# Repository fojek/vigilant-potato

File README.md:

# vigilant-potato
Capteur WiFi générique pour la cabane

* WIFI : ESP-12F ou ESP-M3
* MCU : Atmel ou ESP ou STM
* DC/DC à partir d'une alimentation 24V
* Adresse modifiable, par exemple DIP switch rotative

* Possibilité de lire: 
- distance ; 
- température ; 
- pression ;
- 2 entrées digitales ;

* Possibilité d'écrire :
- deux sorties relais?

Capteur ultrason modulaire (et autres capteurs)

Affichage de l'état : 
 - Vert clignotant : ON et en train de se connecter
 - Vert solide : ON et connecté
 - Autre led : Rouge si erreur (ou la même avec une autre séquence)
 - Autre led : trig effectué (distance)

Todo
- [ ] Déterminer un format
- [ ] Choisir ESP et MCU
- [ ] Choisir capteur ultrason
- [ ] Fabriquer PCB et tester

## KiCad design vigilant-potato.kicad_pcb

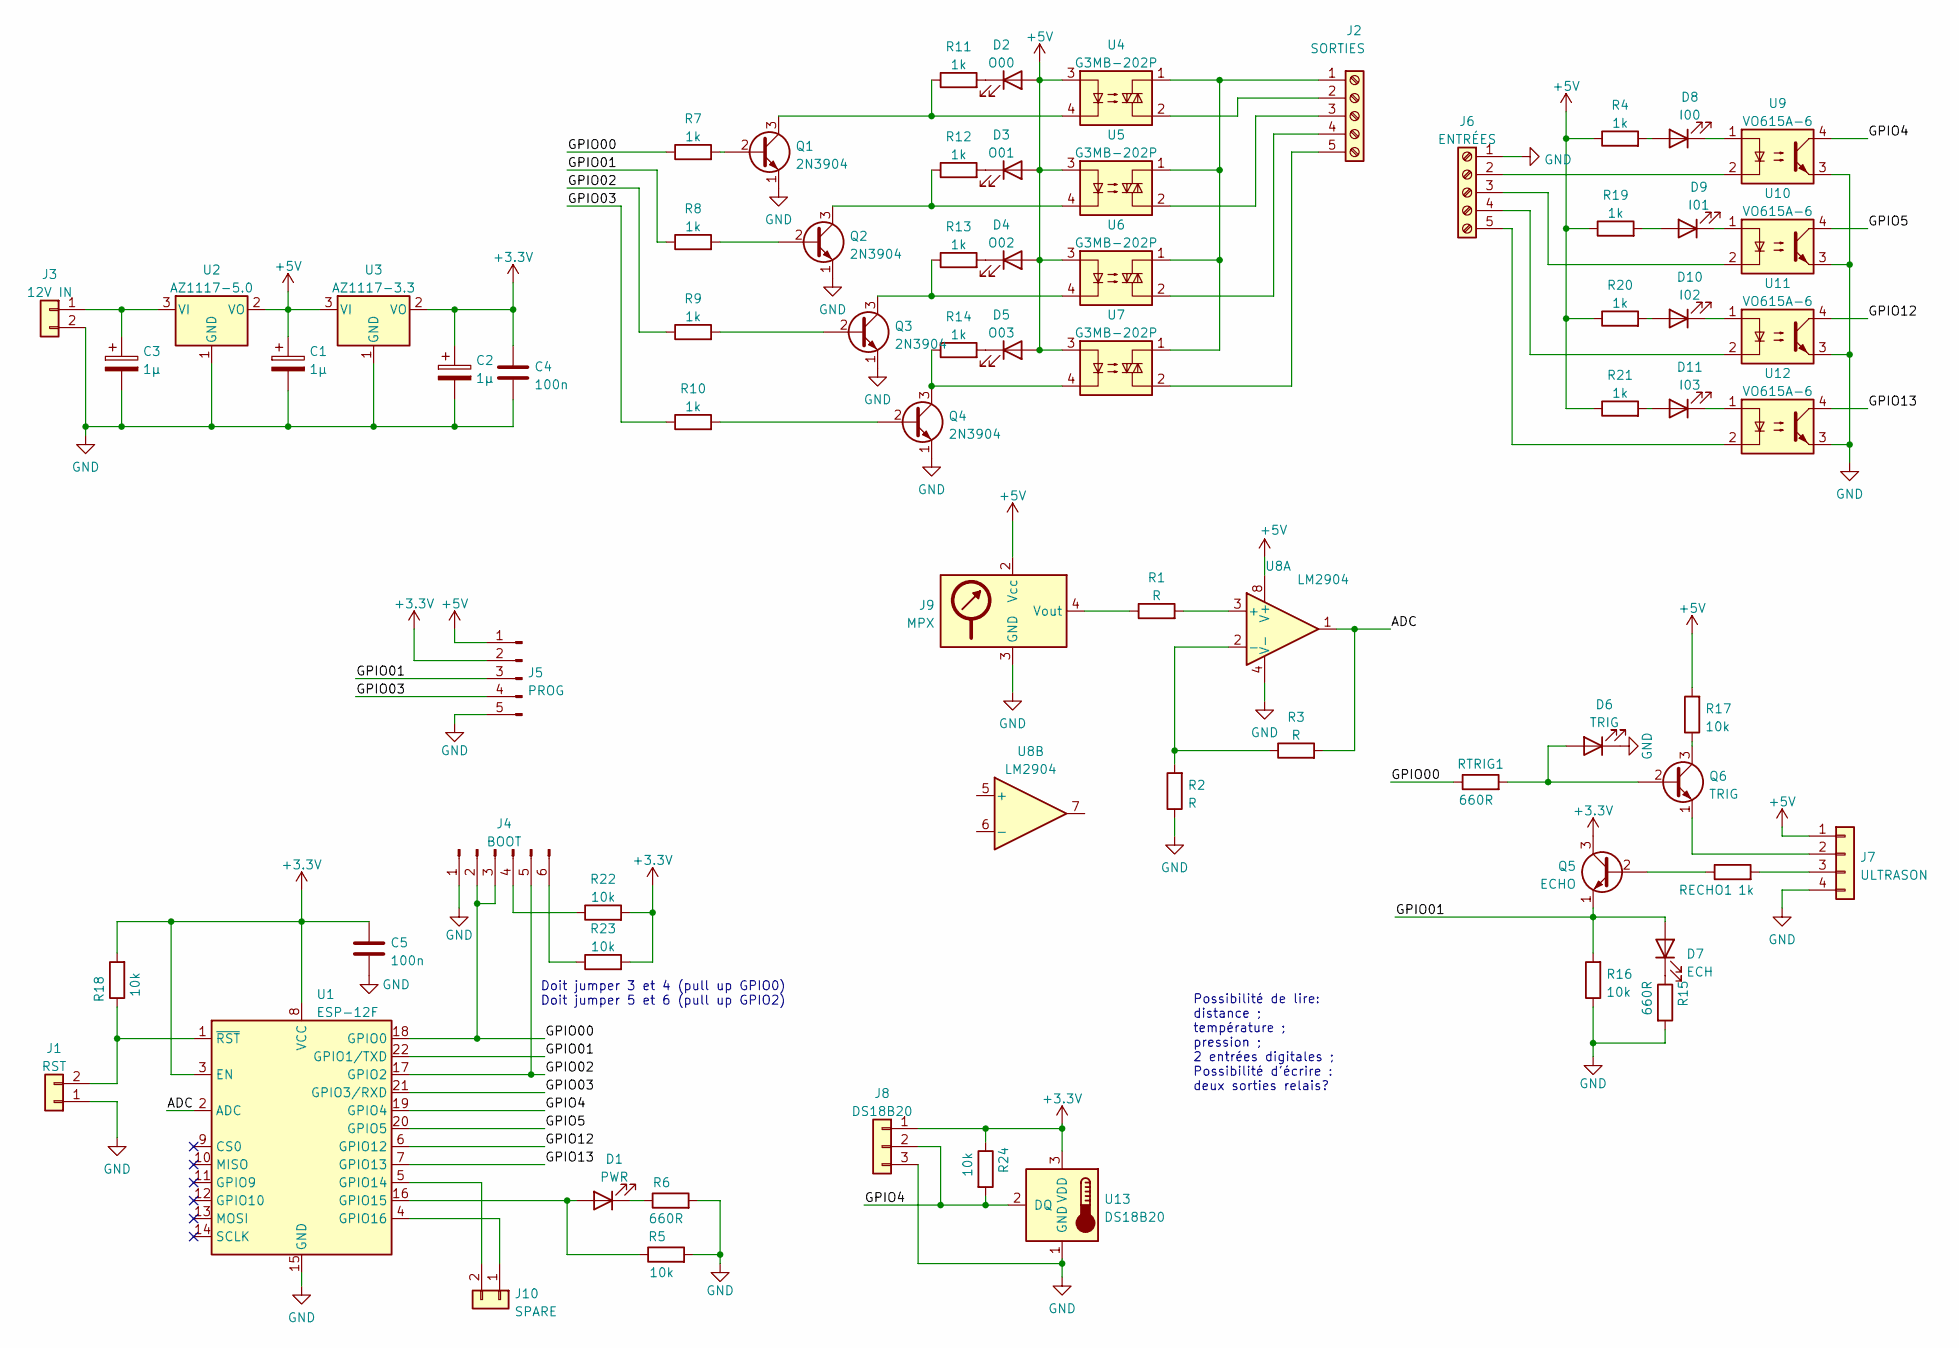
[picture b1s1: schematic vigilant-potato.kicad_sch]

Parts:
C1, C2, C3: 1µ; C_Rect_L7.0mm_W2.0mm_P5.00mm
C4, C5: 100n; C_Rect_L7.0mm_W2.0mm_P5.00mm
D1: PWR; LED_1206_3216Metric_Pad1.42x1.75mm_HandSolder
D2: O00; LED_1206_3216Metric_Pad1.42x1.75mm_HandSolder
D3: O01; LED_1206_3216Metric_Pad1.42x1.75mm_HandSolder
D4: O02; LED_1206_3216Metric_Pad1.42x1.75mm_HandSolder
D5: O03; LED_1206_3216Metric_Pad1.42x1.75mm_HandSolder
D6: TRIG; LED_1206_3216Metric_Pad1.42x1.75mm_HandSolder
D7: ECH; LED_1206_3216Metric_Pad1.42x1.75mm_HandSolder
D8: I00; LED_1206_3216Metric_Pad1.42x1.75mm_HandSolder
D9: I01; LED_1206_3216Metric_Pad1.42x1.75mm_HandSolder
D10: I02; LED_1206_3216Metric_Pad1.42x1.75mm_HandSolder
D11: I03; LED_1206_3216Metric_Pad1.42x1.75mm_HandSolder
J1: RST; PinHeader_1x02_P2.54mm_Vertical
J2: SORTIES; PhoenixContact_MCV_1,5_5-G-3.5_1x05_P3.50mm_Vertical; part EBRA-05-A
J3: 12V IN; PhoenixContact_MCV_1,5_2-G-3.5_1x02_P3.50mm_Vertical; part EBRA-02-A
J4: BOOT; PinHeader_1x06_P2.54mm_Vertical
J5: PROG; PinHeader_1x05_P2.54mm_Vertical
J6: ENTRÉES; PhoenixContact_MCV_1,5_5-G-3.5_1x05_P3.50mm_Vertical; part EBRA-05-A
J7: ULTRASON; PhoenixContact_MCV_1,5_4-G-3.5_1x04_P3.50mm_Vertical; part EBRA-04-A
J8: DS18B20; PinSocket_1x03_P2.54mm_Vertical
J9: MPX; PinHeader_1x06_P2.54mm_Vertical
J10: SPARE; PinHeader_1x02_P2.54mm_Vertical
Q1, Q2, Q3, Q4: 2N3904; TO-92_Inline
Q5: ECHO; TO-92_Inline
Q6: TRIG; TO-92_Inline
R1, R2, R3: R; R_Axial_DIN0207_L6.3mm_D2.5mm_P10.16mm_Horizontal
R4, R11, R12, R13, R14, R19, R20, R21: 1k; R_0805_2012Metric_Pad1.20x1.40mm_HandSolder
R5, R18, R22, R23: 10k; R_0805_2012Metric_Pad1.20x1.40mm_HandSolder
R6: 660R; R_0805_2012Metric_Pad1.20x1.40mm_HandSolder
R7, R8, R9, R10: 1k; R_Axial_DIN0207_L6.3mm_D2.5mm_P10.16mm_Horizontal
R15: 660R; R_Axial_DIN0207_L6.3mm_D2.5mm_P10.16mm_Horizontal
R16, R17, R24: 10k; R_Axial_DIN0207_L6.3mm_D2.5mm_P10.16mm_Horizontal
RECHO1: 1k; R_Axial_DIN0207_L6.3mm_D2.5mm_P10.16mm_Horizontal
RTRIG1: 660R; R_Axial_DIN0207_L6.3mm_D2.5mm_P10.16mm_Horizontal
U1: ESP-12F; ESP-12E
U2: AZ1117-5.0; TO-252-2
U3: AZ1117-3.3; TO-252-2
U4, U5, U6, U7: G3MB-202P
U8: LM2904; SOIC-8_3.9x4.9mm_P1.27mm
U9, U10, U11, U12: VO615A-6; DIP-4_W7.62mm
U13: DS18B20; TO-92_Inline

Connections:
+3.3V: C2.1, C4.1, C5.1, J5.2, J8.1, Q5.3 (C), R18.2, R22.2, R23.2, R24.1, U1.3 (EN), U1.8 (VCC), U3.2 (VO), U13.3 (VDD)
+5V: C1.1, D2.2 (A), D3.2 (A), D4.2 (A), D5.2 (A), J5.1, J7.1, J9.2 (Vcc), R4.1, R17.2, R19.1, R20.1, R21.1, U2.2 (VO), U3.3 (VI), U4.3, U5.3, U6.3, U7.3, U8.8 (V+)
/ADC: R3.2, U1.2 (ADC), U8.1
/GPIO00: J4.2, J4.3, R7.1, RTRIG1.1, U1.18 (GPIO0)
/GPIO01: D7.2 (A), J5.3, Q5.1 (E), R8.1, R16.2, U1.22 (GPIO1/TXD)
/GPIO02: J4.5, R9.1, U1.17 (GPIO2)
/GPIO03: J5.4, R10.1, U1.21 (GPIO3/RXD)
/GPIO4: J8.2, R24.2, U1.19 (GPIO4), U9.4, U13.2 (DQ)
/GPIO5: U1.20 (GPIO5), U10.4
/GPIO12: U1.6 (GPIO12), U11.4
/GPIO13: U1.7 (GPIO13), U12.4
GND: C1.2, C2.2, C3.2, C4.2, C5.2, D6.1 (K), J1.1, J3.2, J4.1, J5.5, J6.1, J7.4, J8.3, J9.3 (GND), Q1.1 (E), Q2.1 (E), Q3.1 (E), Q4.1 (E), R2.1, R5.2, R6.2, R15.2, R16.1, U1.15 (GND), U2.1 (GND), U3.1 (GND), U8.4 (V-), U9.3, U10.3, U11.3, U12.3, U13.1 (GND)
unnamed: C3.1, J3.1, U2.3 (VI)
unnamed: D1.1 (K), R6.1
unnamed: D1.2 (A), R5.1, U1.16 (GPIO15)
unnamed: D2.1 (K), R11.2
unnamed: D3.1 (K), R12.2
unnamed: D4.1 (K), R13.2
unnamed: D5.1 (K), R14.2
unnamed: D6.2 (A), Q6.2 (B), RTRIG1.2
unnamed: D7.1 (K), R15.1
unnamed: D8.1 (K), U9.1
unnamed: D8.2 (A), R4.2
unnamed: D9.1 (K), U10.1
unnamed: D9.2 (A), R19.2
unnamed: D10.1 (K), U11.1
unnamed: D10.2 (A), R20.2
unnamed: D11.1 (K), U12.1
unnamed: D11.2 (A), R21.2
unnamed: J1.2, R18.1, U1.1 (~RST)
unnamed: J2.1, U4.1, U5.1, U6.1, U7.1
unnamed: J2.2, U4.2
unnamed: J2.3, U5.2
unnamed: J2.4, U6.2
unnamed: J2.5, U7.2
unnamed: J4.4, R22.1
unnamed: J4.6, R23.1
unnamed: J6.2, U9.2
unnamed: J6.3, U10.2
unnamed: J6.4, U11.2
unnamed: J6.5, U12.2
unnamed: J7.2, Q6.1 (E)
unnamed: J7.3, RECHO1.2
unnamed: J9.4 (Vout), R1.1
unnamed: J10.1, U1.4 (GPIO16)
unnamed: J10.2, U1.5 (GPIO14)
unnamed: Q1.2 (B), R7.2
unnamed: Q1.3 (C), R11.1, U4.4
unnamed: Q2.2 (B), R8.2
unnamed: Q2.3 (C), R12.1, U5.4
unnamed: Q3.2 (B), R9.2
unnamed: Q3.3 (C), R13.1, U6.4
unnamed: Q4.2 (B), R10.2
unnamed: Q4.3 (C), R14.1, U7.4
unnamed: Q5.2 (B), RECHO1.1
unnamed: Q6.3 (C), R17.1
unnamed: R1.2, U8.3 (+)
unnamed: R2.2, R3.1, U8.2 (-)

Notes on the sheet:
Doit jumper 3 et 4 (pull up GPIO0) Doit jumper 5 et 6 (pull up GPIO2)
Possibilité de lire: distance ; température ; pression ; 2 entrées digitales ; Possibilité d'écrire : deux sorties relais?

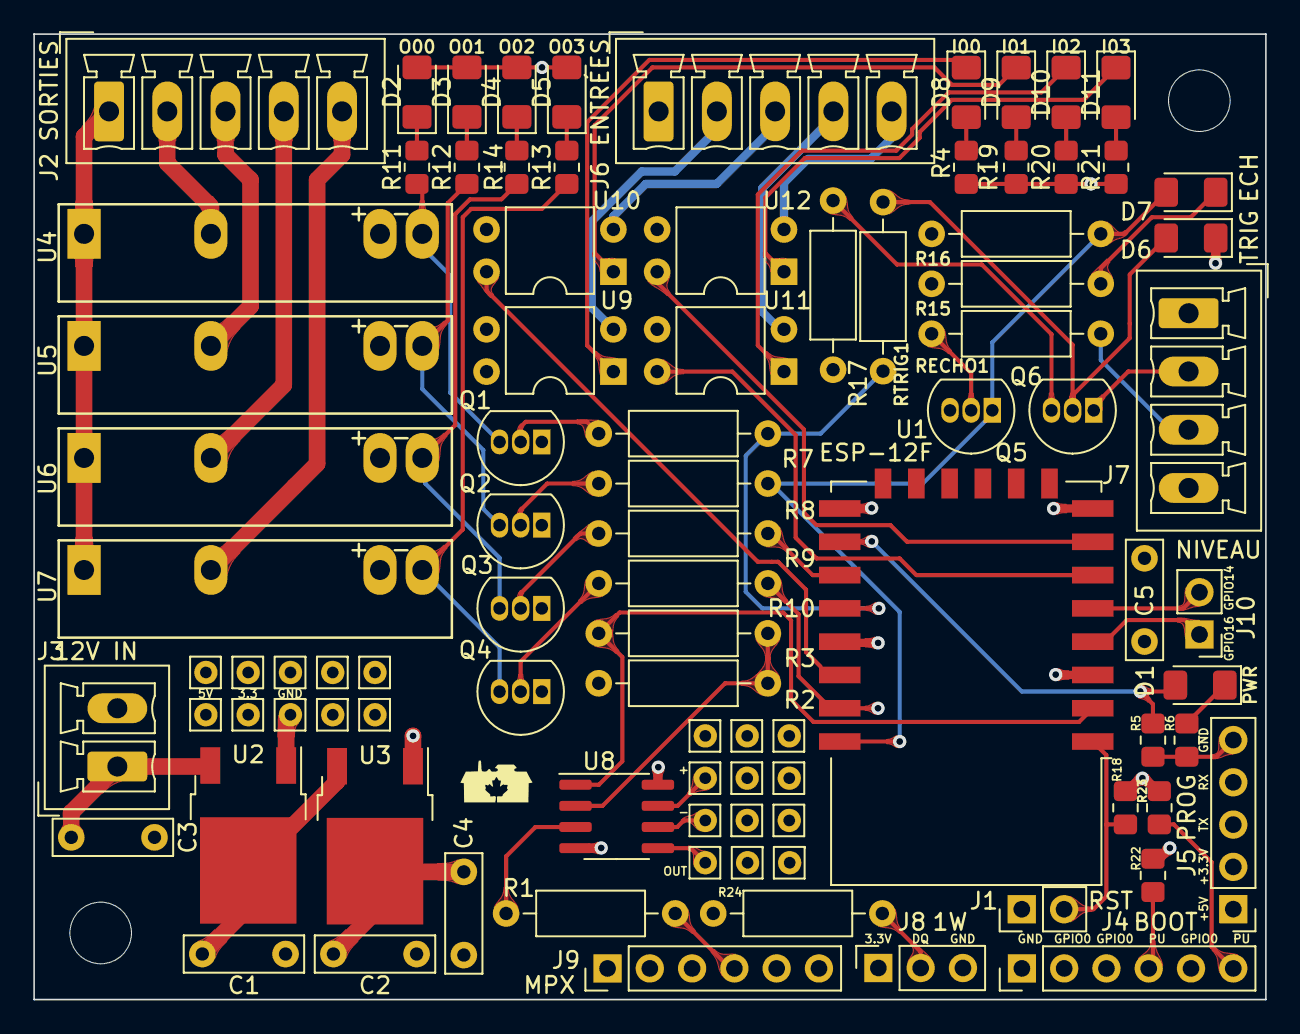
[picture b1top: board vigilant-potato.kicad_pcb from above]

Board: 4 copper layers, 74.0 x 58.0 mm, 73 parts (0 on the bottom side), 58 nets.

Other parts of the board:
+: Pin_D0.7mm_L6.5mm_W1.8mm_FlatFork
-: Pin_D0.7mm_L6.5mm_W1.8mm_FlatFork
OUT: Pin_D0.7mm_L6.5mm_W1.8mm_FlatFork

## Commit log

2023-08-14 Commit initial
